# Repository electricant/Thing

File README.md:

# Thing

Final projects for Robotics exam.

# Objectives

The goal of this project is designing a board to control 5 servomotors,
one for each finger of a [robotic hand](http://inmoov.fr/hand-and-forarm/).
The heart of the project is an atXmega microcontoller which should be able
to set both the current, the angle and the speed of each servo individually.
The hand is also capable of holding things with a user-specified force.

Everything is battery powered and commands can be sent via a WiFi link or
through an USB port. A [ROS](http://www.ros.org/) module will be provided for 
integration with existing or new robotics projects.

A programmer is included within the board for easy firmware upgrade.

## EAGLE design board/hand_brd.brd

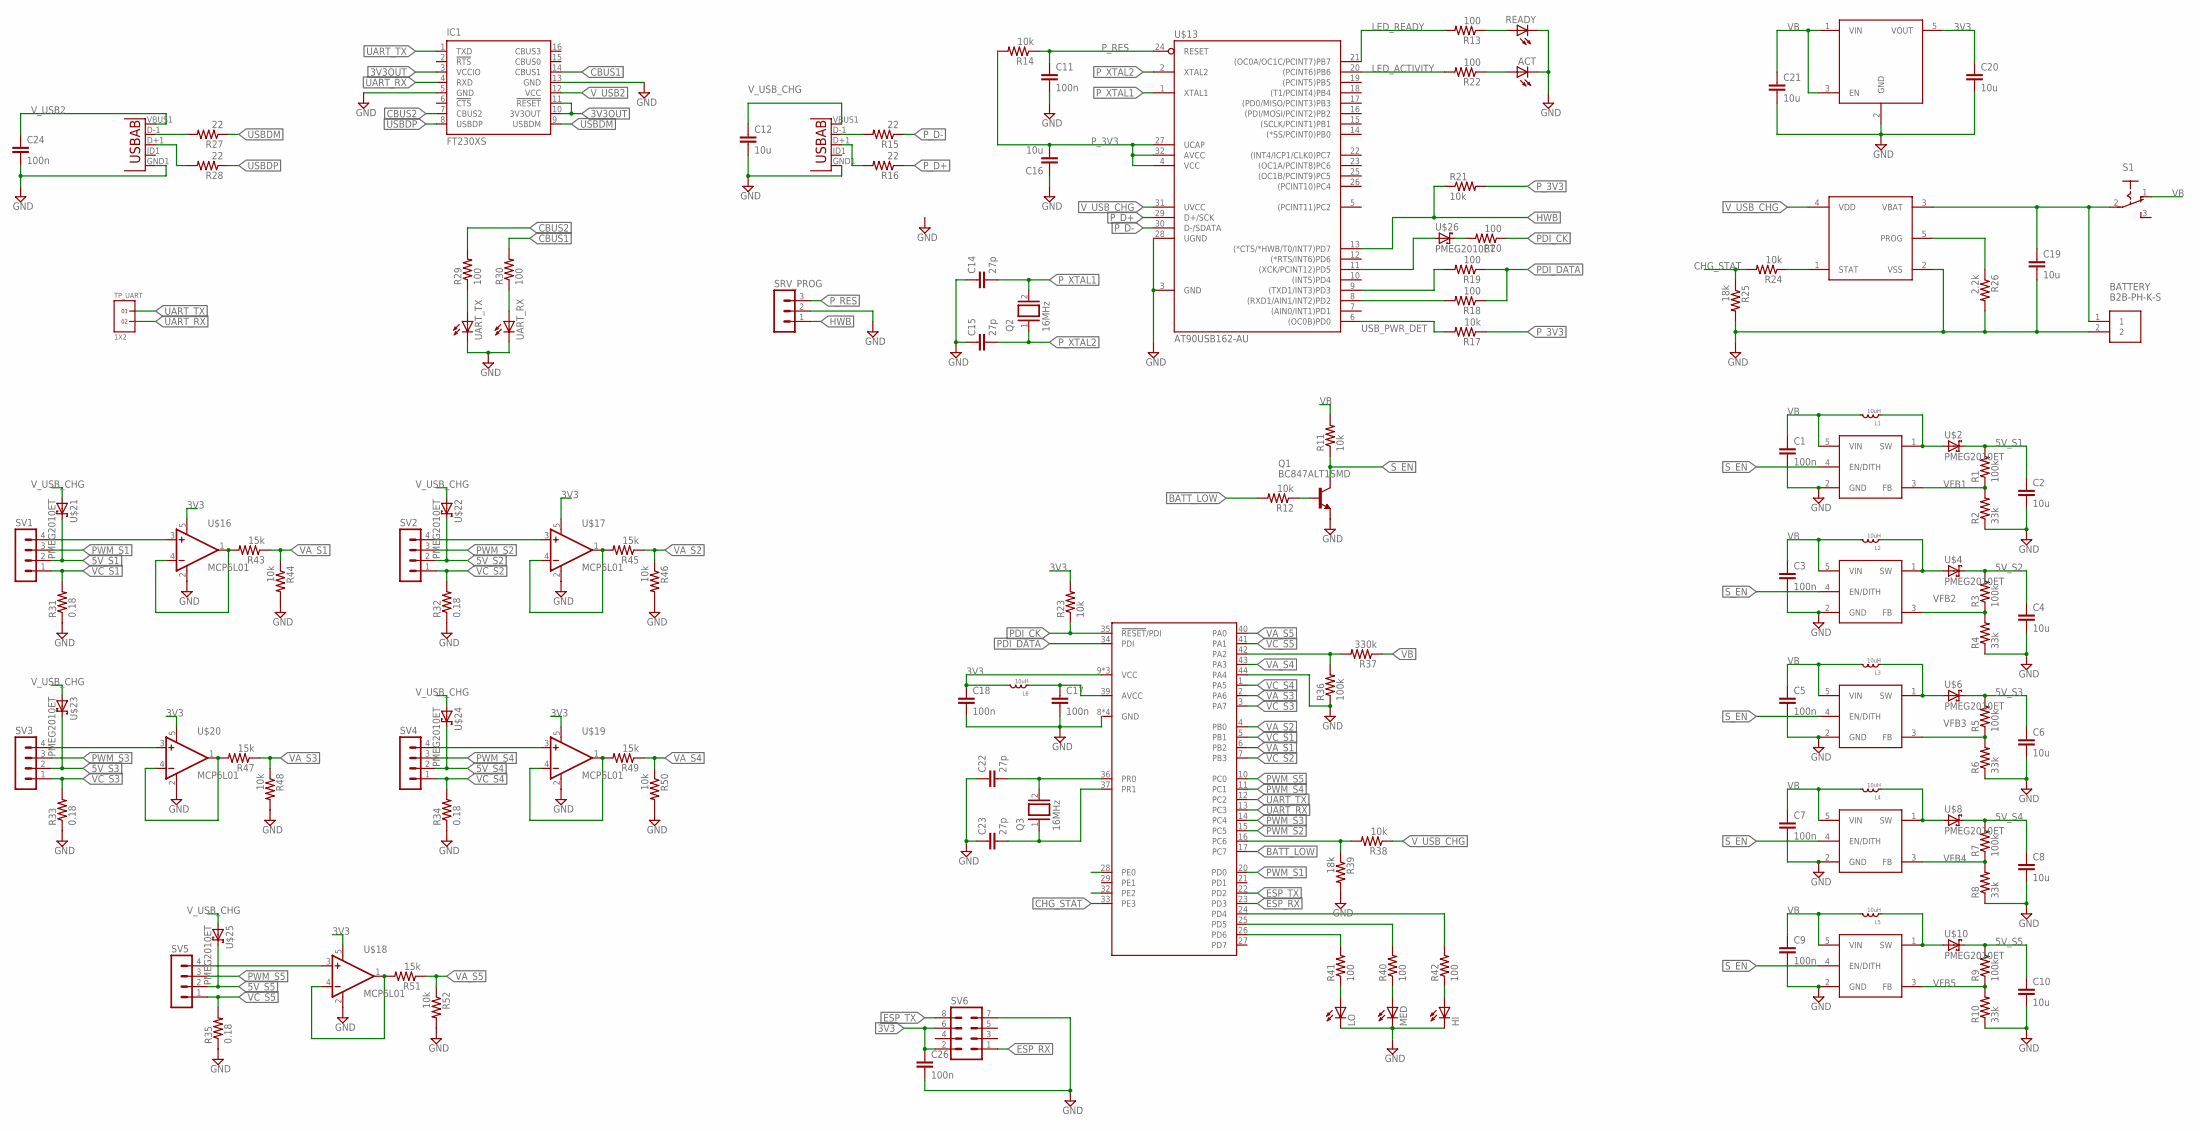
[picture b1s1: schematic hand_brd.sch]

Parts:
ACT: LEDCHIPLED_0805; CHIPLED_0805
BATTERY: B2B-PH-K-S
C1, C3, C5, C7, C9, C11, C17, C18, C24, C26: 100n; C0805K
C2, C4, C6, C8, C10, C12, C16, C19, C20, C21: 10u; C0805K
C14, C15, C22, C23: 27p; C0805K
HI: LEDCHIPLED_0805; CHIPLED_0805
IC1: FT230XS; SSOP16
L1, L2, L3, L4, L5, L6: 10uH; LTF5022
LO: LEDCHIPLED_0805; CHIPLED_0805
MED: LEDCHIPLED_0805; CHIPLED_0805
Q1: BC847ALT1SMD; SOT23
Q2, Q3: 16MHz; QS
R1, R3, R5, R7, R9, R36: 100k; M0805
R2, R4, R6, R8, R10: 33k; M0805
R11, R12, R14, R17, R21, R23, R24, R38, R44, R46, R48, R50, R52: 10k; M0805
R13, R18, R19, R20, R22, R29, R30, R40, R41, R42: 100; M0805
R15, R16, R27, R28: 22; M0805
R25, R39: 18k; M0805
R26: 2.2k; M0805
R31, R32, R33, R34, R35: 0.18; M0805
R37: 330k; M0805
R43, R45, R47, R49, R51: 15k; M0805
READY: LEDCHIPLED_0805; CHIPLED_0805
S1: 255SB
SRV_PROG: MA03-1
SV1, SV2, SV3, SV4, SV5: MA04-1
SV6: MA04-2
TP_UART: 1X2
U1, U3: USB""; USB-MICRO-SMD
U2: ATXMEGA128D4-AU; TQFP-44A-44
U$1, U$3, U$5, U$7, U$9: MIC2250-2YD5; SOT23-5
U$2, U$4, U$6, U$8, U$10, U$21, U$22, U$23, U$24, U$25, U$26: PMEG2010ET; SOT23
U$13: AT90USB162-AU; TQFP32-08
U$14: MCP73831; SOT23-5
U$15: MIC5504; SOT23-5
U$16, U$17, U$18, U$19, U$20: MCP6L01; SOT23-5
UART_RX: LEDCHIPLED_0805; CHIPLED_0805
UART_TX: LEDCHIPLED_0805; CHIPLED_0805

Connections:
3V3: C18.1, C20.1, C26.1, L6.P$2 (2), R23.2, SV6.2, SV6.6, U2.9 (VCC), U2.19 (VCC), U2.31 (VCC), U$15.5 (VOUT), U$16.5 (V+), U$17.5 (V+), U$18.5 (V+), U$19.5 (V+), U$20.5 (V+)
3V3OUT: IC1.3 (VCCIO), IC1.10 (3V3OUT), IC1.11 (!RESET)
5V_S1: C2.1, R1.2, SV1.2, U$2.3 (C), U$21.3 (C)
5V_S2: C4.1, R3.2, SV2.2, U$4.3 (C), U$22.3 (C)
5V_S3: C6.1, R5.2, SV3.2, U$6.3 (C), U$23.3 (C)
5V_S4: C8.1, R7.2, SV4.2, U$8.3 (C), U$24.3 (C)
5V_S5: C10.1, R9.2, SV5.2, U$10.3 (C), U$25.3 (C)
BATT_LOW: R12.2, U2.17 (PC7)
CBUS1: IC1.14 (CBUS1), R30.2
CBUS2: IC1.7 (CBUS2), R29.2
CHG_STAT: R24.2, R25.1, U2.33 (PE3)
ESP_RX: SV6.1, U2.23 (PD3)
ESP_TX: SV6.8, U2.22 (PD2)
GND: ACT.C, BATTERY.2, C1.2, C2.2, C3.2, C4.2, C5.2, C6.2, C7.2, C8.2, C9.2, C10.2, C11.2, C12.2, C14.1, C15.1, C16.1, C17.2, C18.2, C19.2, C20.2, C21.2, C22.1, C23.1, C24.2, C26.2, HI.C, IC1.5 (GND), IC1.13 (GND), LO.C, MED.C, Q1.2 (E), R2.1, R4.1, R6.1, R8.1, R10.1, R25.2, R26.2, R31.1, R32.1, R33.1, R34.1, R35.1, R36.1, R39.2, R44.2, R46.2, R48.2, R50.2, R52.2, READY.C, SRV_PROG.2, SV6.7, U1.GND1 (GND), U2.8 (GND), U2.18 (GND), U2.30 (GND), U2.38 (GND), U2.44 (PA4), U3.GND1 (GND), U$1.2 (GND), U$3.2 (GND), U$5.2 (GND), U$7.2 (GND), U$9.2 (GND), U$13.3 (GND), U$13.28 (UGND), U$14.2 (VSS), U$15.2 (GND), U$16.2 (V-), U$17.2 (V-), U$18.2 (V-), U$19.2 (V-), U$20.2 (V-), UART_RX.C, UART_TX.C
HWB: R21.1, SRV_PROG.1, U$13.13 ((*CTS/*HWB/T0/INT7)PD7)
LED_ACTIVITY: R22.2, U$13.20 ((PCINT6)PB6)
LED_READY: R13.2, U$13.21 ((OC0A/OC1C/PCINT7)PB7)
unnamed: L2.P$1 (1), U$3.1 (SW), U$4.1 (A)
unnamed: L1.P$1 (1), U$1.1 (SW), U$2.1 (A)
unnamed: R18.2, U$13.8 ((RXD1/AIN1/INT2)PD2)
unnamed: L3.P$1 (1), U$5.1 (SW), U$6.1 (A)
unnamed: Q1.1 (B), R12.1
unnamed: L4.P$1 (1), U$7.1 (SW), U$8.1 (A)
unnamed: R16.2, U3.D+1 (D+)
unnamed: L5.P$1 (1), U$9.1 (SW), U$10.1 (A)
unnamed: R15.2, U3.D-1 (D-)
unnamed: R20.2, U$26.3 (C)
unnamed: R19.2, U$13.9 ((TXD1/INT3)PD3)
unnamed: U$13.11 ((XCK/PCINT12)PD5), U$26.1 (A)
unnamed: R13.1, READY.A
unnamed: ACT.A, R22.1
unnamed: C17.1, L6.P$1 (1), U2.39 (AVCC)
unnamed: R27.2, U1.D-1 (D-)
unnamed: R24.1, U$14.1 (STAT)
unnamed: R26.1, U$14.5 (PROG)
unnamed: BATTERY.1, C19.1, S1.2, U$14.3 (VBAT)
unnamed: R28.2, U1.D+1 (D+)
unnamed: R29.1, UART_TX.A
unnamed: R30.1, UART_RX.A
unnamed: R36.2, R37.2, U2.42 (PA2)
unnamed: R38.2, R39.1, U2.16 (PC6)
unnamed: SV2.4, U$17.3 (+IN)
unnamed: SV1.4, U$16.3 (+IN)
unnamed: SV5.4, U$18.3 (+IN)
unnamed: MED.A, R40.1
unnamed: SV3.4, U$20.3 (+IN)
unnamed: SV4.4, U$19.3 (+IN)
unnamed: LO.A, R41.1
unnamed: HI.A, R42.1
unnamed: R41.2, U2.26 (PD6)
unnamed: R40.2, U2.25 (PD5)
unnamed: R42.2, U2.24 (PD4)
unnamed: R45.2, U$17.1 (OUT), U$17.4 (-IN)
unnamed: R43.2, U$16.1 (OUT), U$16.4 (-IN)
unnamed: R47.2, U$20.1 (OUT), U$20.4 (-IN)
unnamed: R49.2, U$19.1 (OUT), U$19.4 (-IN)
unnamed: R51.2, U$18.1 (OUT), U$18.4 (-IN)
PDI_CK: R20.1, R23.1, U2.35 (!RESET!/PDI)
PDI_DATA: R18.1, R19.1, U2.34 (PDI)
PWM_S1: SV1.3, U2.20 (PD0)
PWM_S2: SV2.3, U2.15 (PC5)
PWM_S3: SV3.3, U2.14 (PC4)
PWM_S4: SV4.3, U2.11 (PC1)
PWM_S5: SV5.3, U2.10 (PC0)
P_3V3: C16.2, R14.2, R17.1, R21.2, U$13.4 (VCC), U$13.27 (UCAP), U$13.32 (AVCC)
P_D+: R16.1, U$13.29 (D+/SCK)
P_D-: R15.1, U$13.30 (D-/SDATA)
P_RES: C11.1, R14.1, SRV_PROG.3, U$13.24 (RESET)
P_XTAL1: C14.2, Q2.2, U$13.1 (XTAL1)
P_XTAL2: C15.2, Q2.1, U$13.2 (XTAL2)
S_EN: Q1.3 (C), R11.1, U$1.4 (EN/DITH), U$3.4 (EN/DITH), U$5.4 (EN/DITH), U$7.4 (EN/DITH), U$9.4 (EN/DITH)
UART_RX: IC1.4 (RXD), TP_UART.2, U2.13 (PC3)
UART_TX: IC1.1 (TXD), TP_UART.1, U2.12 (PC2)
USBDM: IC1.9 (USBDM), R27.1
USBDP: IC1.8 (USBDP), R28.1
USB_PWR_DET: R17.2, U$13.6 ((OC0B)PD0)
VA_S1: R43.1, R44.1, U2.6 (PB2)
VA_S2: R45.1, R46.1, U2.4 (PB0)
VA_S3: R47.1, R48.1, U2.2 (PA6)
VA_S4: R49.1, R50.1, U2.43 (PA3)
VA_S5: R51.1, R52.1, U2.40 (PA0)
VB: C1.1, C3.1, C5.1, C7.1, C9.1, C21.1, L1.P$2 (2), L2.P$2 (2), L3.P$2 (2), L4.P$2 (2), L5.P$2 (2), R11.2, R37.1, S1.1 (O), U$1.5 (VIN), U$3.5 (VIN), U$5.5 (VIN), U$7.5 (VIN), U$9.5 (VIN), U$15.1 (VIN), U$15.3 (EN)
VC_S1: R31.2, SV1.1, U2.5 (PB1)
VC_S2: R32.2, SV2.1, U2.7 (PB3)
VC_S3: R33.2, SV3.1, U2.3 (PA7)
VC_S4: R34.2, SV4.1, U2.1 (PA5)
VC_S5: R35.2, SV5.1, U2.41 (PA1)
VFB1: R1.1, R2.2, U$1.3 (FB)
VFB2: R3.1, R4.2, U$3.3 (FB)
VFB3: R5.1, R6.2, U$5.3 (FB)
VFB4: R7.1, R8.2, U$7.3 (FB)
VFB5: R9.1, R10.2, U$9.3 (FB)
V_USB2: C24.1, IC1.12 (VCC), U1.VBUS1 (VBUS)
V_USB_CHG: C12.1, R38.1, U3.VBUS1 (VBUS), U$13.31 (UVCC), U$14.4 (VDD), U$21.1 (A), U$22.1 (A), U$23.1 (A), U$24.1 (A), U$25.1 (A)
XTAL1: C22.2, Q3.2, U2.36 (PR0)
XTAL2: C23.2, Q3.1, U2.37 (PR1)

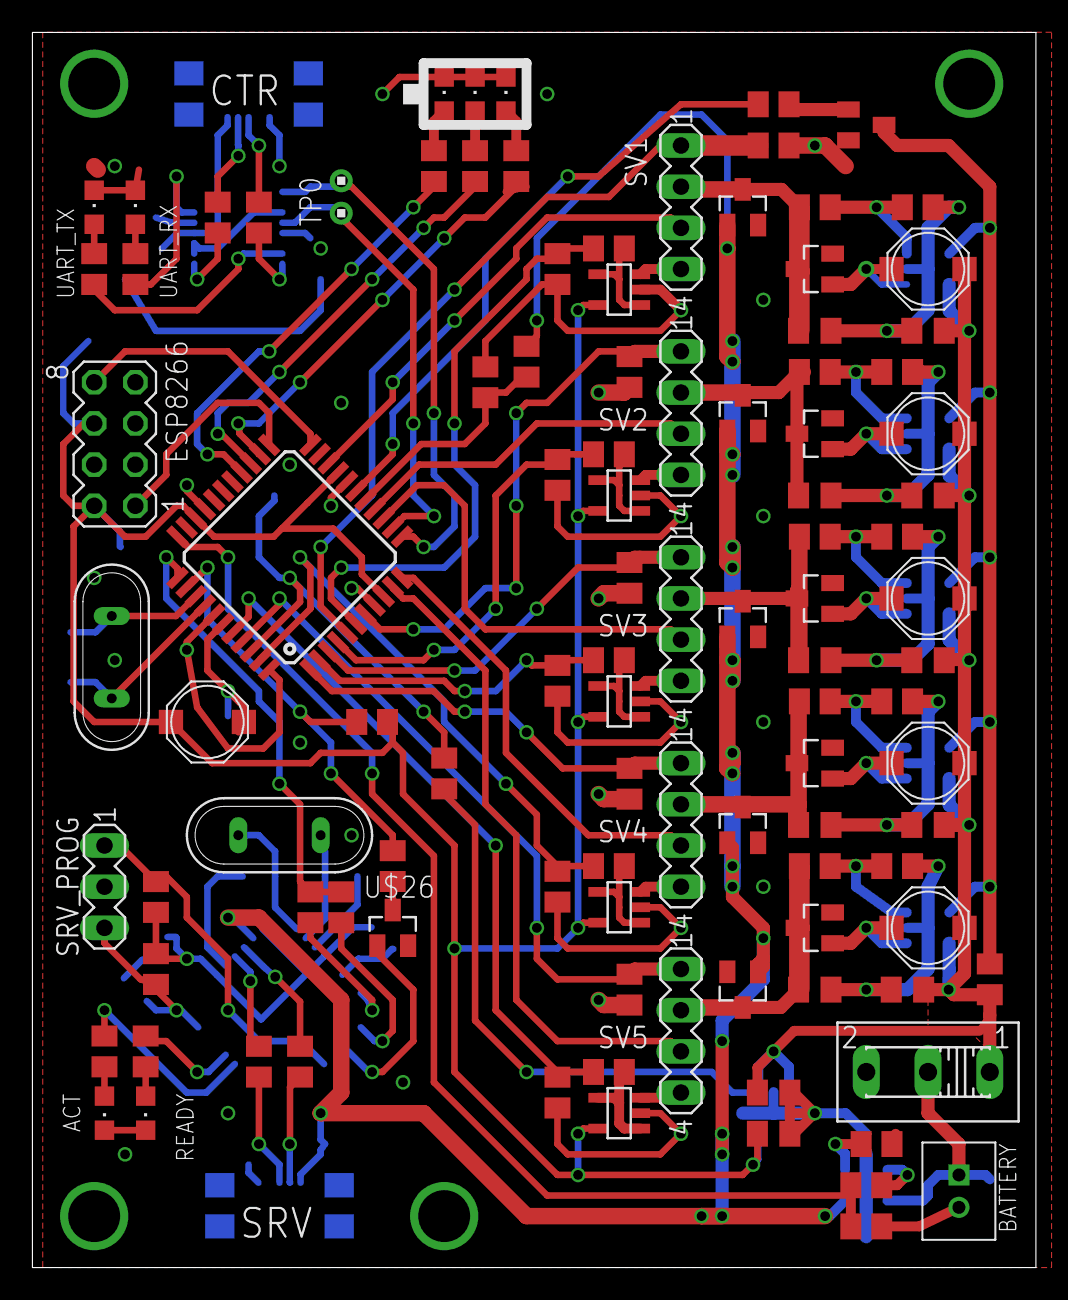
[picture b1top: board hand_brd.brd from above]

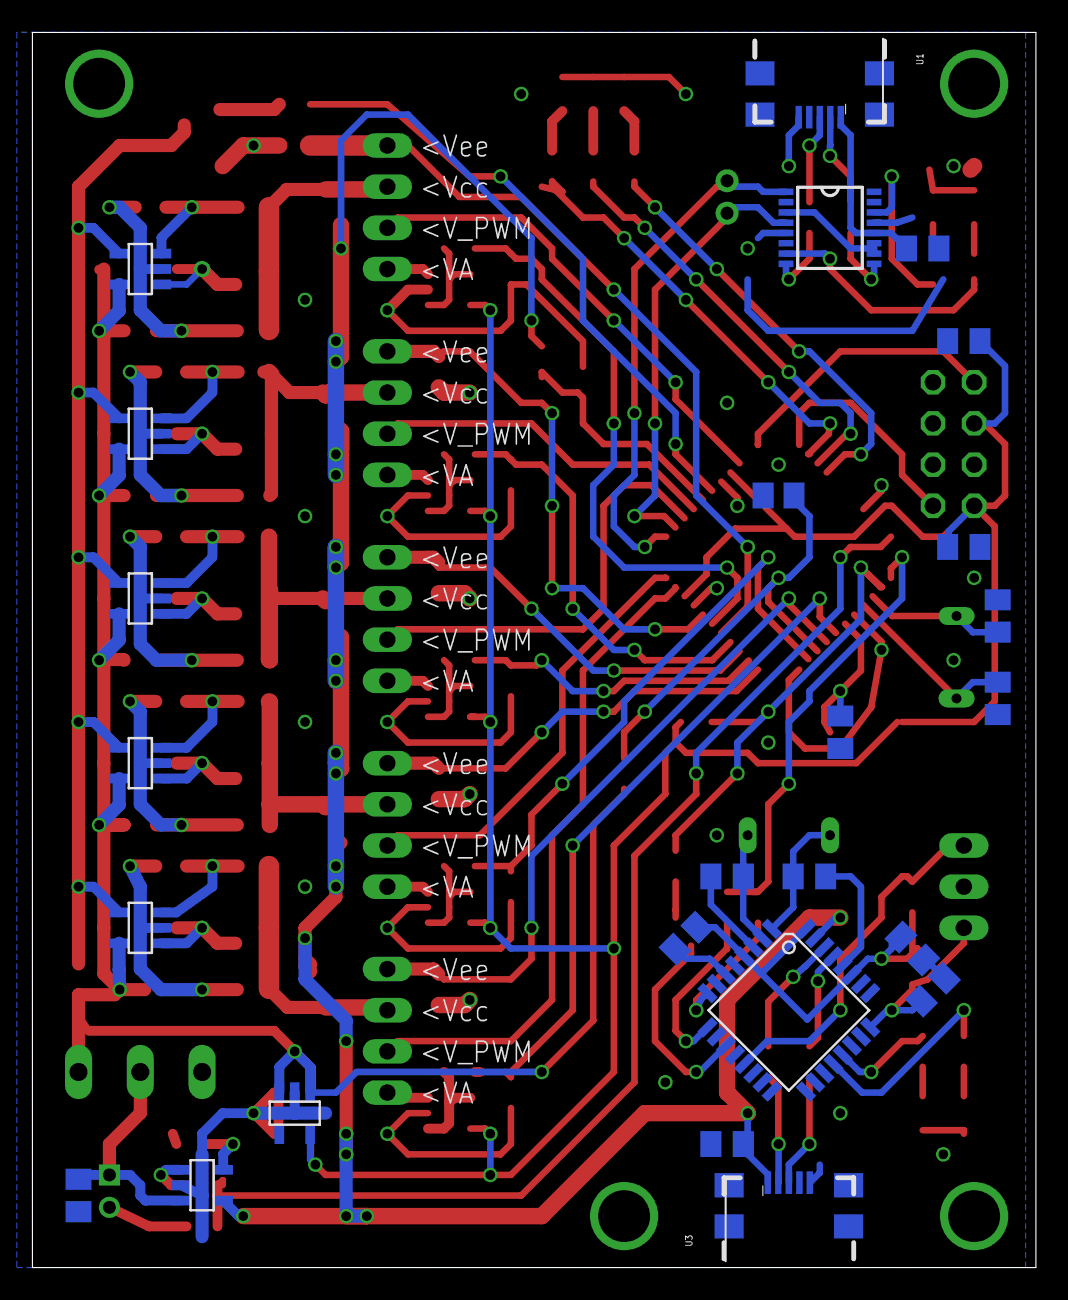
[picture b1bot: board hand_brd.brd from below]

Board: 2 copper layers, 61.9 x 76.2 mm, 130 parts (25 on the bottom side), 96 nets.

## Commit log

2016-06-25 Add firmware source code
2016-06-25 update gitignore
2016-06-25 Add schematic and layout
2016-06-25 Remove huge datasheets. Better not put it on github
2016-06-25 Update readme once more
2016-06-25 Add missing link to the ROS website
2016-06-25 Some minor refactoring
2016-06-25 Prepare the ground for using multiple servos
2016-06-26 Ignore vim swap files
2016-06-26 Enable three different operating modes for the servo driver.
2016-06-26 The correct value for the CC register was not always set+
2016-06-27 Add tests for the shiny-new protocol (coming soon)
2016-06-29 New protocol! Not always working due to parsing issues
2016-07-02 Fix wrong USB model
2016-07-03 Add micro usb pinout detail
2016-07-03 Create gerber files from the updated board
2016-07-03 The serio driver is now able to send data through the serial port
2016-07-03 Make the driver status variable volatile
2016-07-03 Introduce the new command parser and interpreter for the messages coming through the WiFi link
2016-07-03 Recognize when no servo is supplied as an argument and the user is trying to modify some parameters
2016-07-09 make speed fractional to slow down servo motion
2016-07-09 Add commands for reading servo variables from the wifi link
2016-07-09 Send commands from the board to the controlling application using WiFi
2016-07-12 Add test program for the new commands
2016-07-12 explain endianess
2016-07-12 Fix data sending which was not working due to a typo and a wrong interrupt level
2016-07-13 rework esp_driver a bit in order to use interrupts
2016-07-14 fix issues with the WiFi driver. Now it should work correctly
2016-07-15 update BOM
2016-07-16 Add missing diode
2016-07-17 Port the code to the new board
2016-07-17 continue porting
2016-07-17 Use the shiny-new ADC driver with the old servo driver
2016-07-17 Add battery driver to control the carge status
2016-07-18 Fix wrong detection of low battery and disable the converters when external powered
2016-07-18 Forgotten to add the battery driver files. Here they are
2016-07-18 Remove unused connection for disabling the boost converters and shuffle things around a bit to have a better ground plane
2016-07-19 Enable the external crystal oscillator
2016-07-19 Fix missing port initialization
2016-07-19 Add clksys drivers
2016-07-19 Try to fix the current measuring with no result
2016-07-20 Fix TheADC driver a bit. I have still no clue why the measurements seem to be incorrect
2016-07-20 Send the command back as an ACK
2016-07-20 Fix missing curly braces
2016-07-20 Use the new ACK mechanism in testwifi
2016-07-20 Avoid power surges by setting the status of each servo immediately. Wait for updates instead
2016-07-20 Fail silently if setting values on an invalid servo
2016-07-20 Increase default maximum current
2016-07-20 Revert changes to the ADC driver. Still not working :(
2016-07-22 Add missing method declaration
2016-07-25 Add some documentation. Only in italian now. Maybe it will be translated
